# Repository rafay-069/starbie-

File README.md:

# Starbie 

A 3D-printed Yeti desktop companion robot powered by an ESP32-C3 microcontroller, featuring interactive animations, environmental monitoring, voice response, and an I2S audio amplifier setup i was inspired by jarvis from ironman so instead of making it simple starie i made changes i wanted to be more creative 

## Hardware Components
- Seeed Studio XIAO ESP32-C3
- 0.96" I2C OLED Display (SSD1306)
- GY-521 MPU-6050 6-DOF Motion Sensor
- SmartElex MAX98357A I2S Amplifier Breakout
- 30mm 8 Ohm 0.5W Mini Speaker
- INMP441 MEMS I2S Microphone
- DHT11 Temperature & Humidity Sensor
- 3.7V 500mAh 1S LiPo Battery
- ## MY CIRCUIT 

##  Bill of Materials (BOM)

## Bill of Materials (BOM)

| # | Component | Description / Function | Qty | Unit Price | Total | Vendor |
| :-: | :--- | :--- | :-: | :-: | :-: | :--- |
| **1** | **Seeed Studio XIAO ESP32–C3** | Main MCU running logic, Wi-Fi & BLE | 1 | $6.80 | $6.80 | [Robu.in](https://robu.in/product/seeed-studio-xiao-esp32c3-tiny-mcu-board-with-wi-fi-and-ble-battery-charge-supported-power-efficiency-and-rich-interface/) |
| **2** | **0.96" I2C OLED Display (SSD1306)** | 128×64 screen for animated face & UI | 1 | $2.00 | $2.00 | [Robu.in](https://robu.in/product/0-96-inch-i2c-iic-4pin-oled-display-module-black/) |
| **3** | **GY-521 MPU-6050 6-DOF IMU** | 3-axis gyro + accelerometer for motion detection | 1 | $1.60 | $1.60 | [Robu.in](https://robu.in/product/mpu-6050-gyro-sensor-2-accelerometer/) |
| **4** | **DHT11 Sensor Module (3-pin)** | Temperature and humidity sensing | 1 | $1.00 | $1.00 | [Robu.in](https://robu.in/product/dht11-digital-relative-humidity-temperature-sensor-module/) |
| **5** | **6×6×5mm Tactile Buttons (5-pack)** | Physical buttons for feeding & menu action | 1 | $0.30 | $0.30 | [Robu.in](https://robu.in/product/6x6x5mm-tactile-push-button-switch/) |
| **6** | **INMP441 MEMS I2S Microphone** | Digital audio capture for sound/voice commands | 1 | $1.80 | $1.80 | [Robu.in](https://robu.in/product/inmp441-mems-high-precision-omnidirectional-microphone-module-i2s/) |
| **7** | **3.7V 500mAh 1S LiPo Battery** | PCM protected cordless power pack | 1 | $3.50 | $3.50 | [Robu.in](https://robu.in/product/500mah-pcm-protected-micro-li-po-battery/) |
| **8** | **0805 SMD 0.1 µF Ceramic Capacitors** | Rail decoupling filters for MCU & mic (10-pack) | 1 | $0.20 | $0.20 | [Robu.in](https://robu.in/product/100nf-0805-surface-mount-multilayer-ceramic-capacitor-pack-of-40/) |
| **9** | **1×40 Pin 2.54 mm Male Header Strip** | Breakaway pins for module mounting | 1 | $0.15 | $0.15 | [Robu.in](https://robu.in/product/1x40-pin-2-54-pitch-male-berg-strip/) |
| **10** | **SmartElex MAX98357A I2S Amplifier** | 3W Class-D digital amplifier for voice output | 1 | $2.00 | $2.00 | [Robu.in](https://robu.in/product/smartelex-i2s-audio-breakout-max98357a/) |
| **11** | **INGHAi 30mm 8Ω 0.5W Mini Speaker** | Compact speaker for sound effects & chirps | 1 | $2.00 | $2.00 | [Robu.in](https://robu.in/product/gspk3005tn-8r0-5w-inghai-d30h5-0mm-round-8-ohm-0-5w-85-3db/) |
| — | **Taxes & Shipping** | Estimated shipping and handling | — | — | $5.90 | Robu.in |
| — | **Total Project Cost** | **Tier 1 Grant Funding Budget** | — | — | **$29.05** | — |
---

## ⚡ Circuit & PCB Design

### Schematic

I HAVE A BUZZER THATS WHY I DIDNT ADD IT IN BOM AND ALSO I WILL BE USING SPEAKERS MAINLY 

## Repository Structure
- `bom.csv`: Bill of Materials for grant verification
- `journal.md`: Daily progress logs and build documentation
- `pcb/`: KiCad schematic and layout files
- `firmware/`: ESP32-C3 source code

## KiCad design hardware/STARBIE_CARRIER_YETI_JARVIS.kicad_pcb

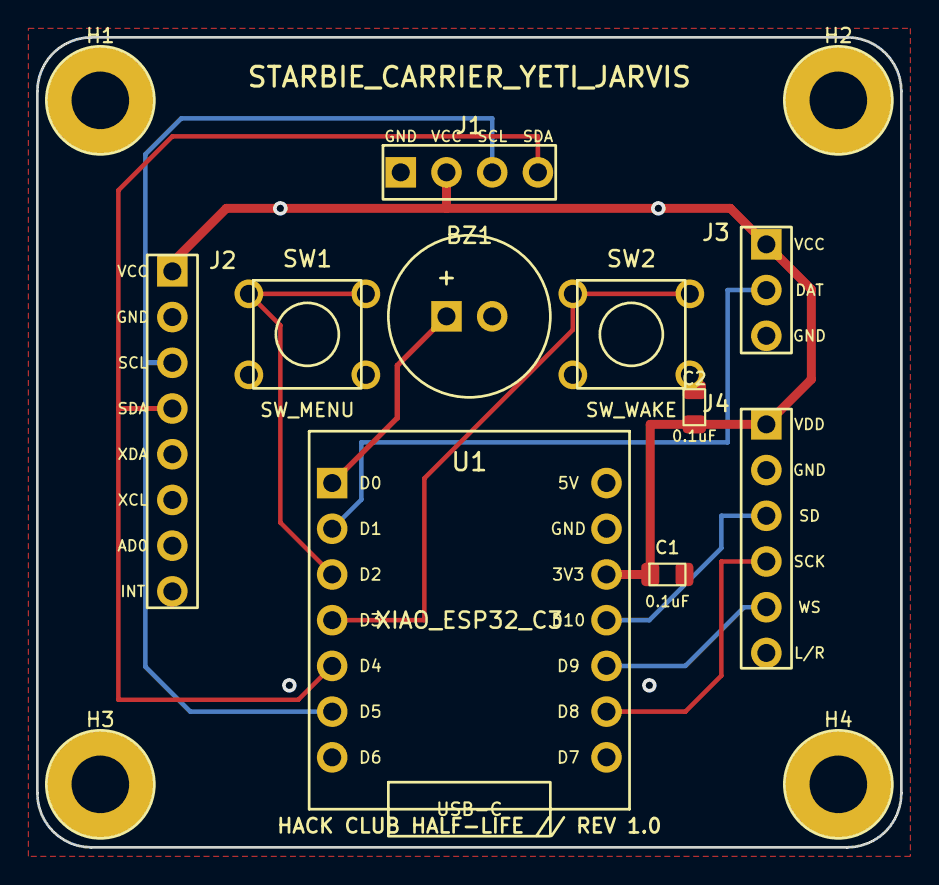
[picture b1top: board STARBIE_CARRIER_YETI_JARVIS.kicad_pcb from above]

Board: 2 copper layers, 48.0 x 45.0 mm, 14 parts (0 on the bottom side), 11 nets.

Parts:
BZ1: Buzzer; Buzzer_12x9.5RM7.6
C1, C2: 0.1uF; C_0805_2012Metric
H1, H2, H3, H4: MountingHole_M3; MountingHole_3.2mm_M3_Pad_Via
J1: OLED_SSD1306; PinHeader_1x04_P2.54mm_Horizontal
J2: GY-521_MPU6050; PinHeader_1x08_P2.54mm_Vertical
J3: DHT11; PinHeader_1x03_P2.54mm_Vertical
J4: INMP441_MIC; PinHeader_1x06_P2.54mm_Vertical
SW1: SW_MENU; SW_PUSH_6mm
SW2: SW_WAKE; SW_PUSH_6mm
U1: XIAO_ESP32_C3; Seeed_XIAO_DIP14

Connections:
+3V3: C1.1, C2.1, J1.2, J2.1, J3.1, J4.1, U1.12
BTN_1: SW1.1, SW1.2, U1.3
BTN_2: SW2.1, SW2.2, U1.4
BUZZER: BZ1.1, U1.1
DHT_DATA: J3.2, U1.2
GND: BZ1.2, C1.2, C2.2, H1.1, H2.1, H3.1, H4.1, J1.1, J2.2, J2.7, J3.3, J4.2, J4.6, SW1.3, SW1.4, SW2.3, SW2.4, U1.13
I2C_SCL: J1.3, J2.3, U1.6
I2C_SDA: J1.4, J2.4, U1.5
I2S_SCK: J4.4, U1.9
I2S_SD: J4.3, U1.11
I2S_WS: J4.5, U1.10
